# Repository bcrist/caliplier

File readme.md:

# Digital Caliper USB interface & LED Display

This project interfaces with the serial data output port found on cheap digital calipers.  It does several things:

* Provides power to the calipers
* Provides a second readout which isn't physically constrained by the measurement location/orientation
* Emulates a USB HID keyboard and "types" the current measurement at the press of a button
* Emulates a USB CDC-ACM serial port for logging/debug

There are many different variations on the serial format output by different calipers.  Some use 24-bit integers, some use BCD.  Some always output in inches, some always in mm, and some in whatever format the internal display is currently using.  Some include error detection data, others don't.  Currently there is only one protocol supported:

* Data signal is stable whenever Clock signal is high
* 24-bit packet, transferred over 8.1ms (+/- 0.1ms)
* First bit is always 1
* Next 20 bits are the unsigned magnitude (little-endian)
* Next bit is 1 if negative
* Last two bits are unused
* There is no indication whether it is in mm or inches mode.  In mm mode, 1 ULP is 0.01mm, and in inches mode, 1 ULP is 0.0005".
* The bus is idle for at least 5ms between packets

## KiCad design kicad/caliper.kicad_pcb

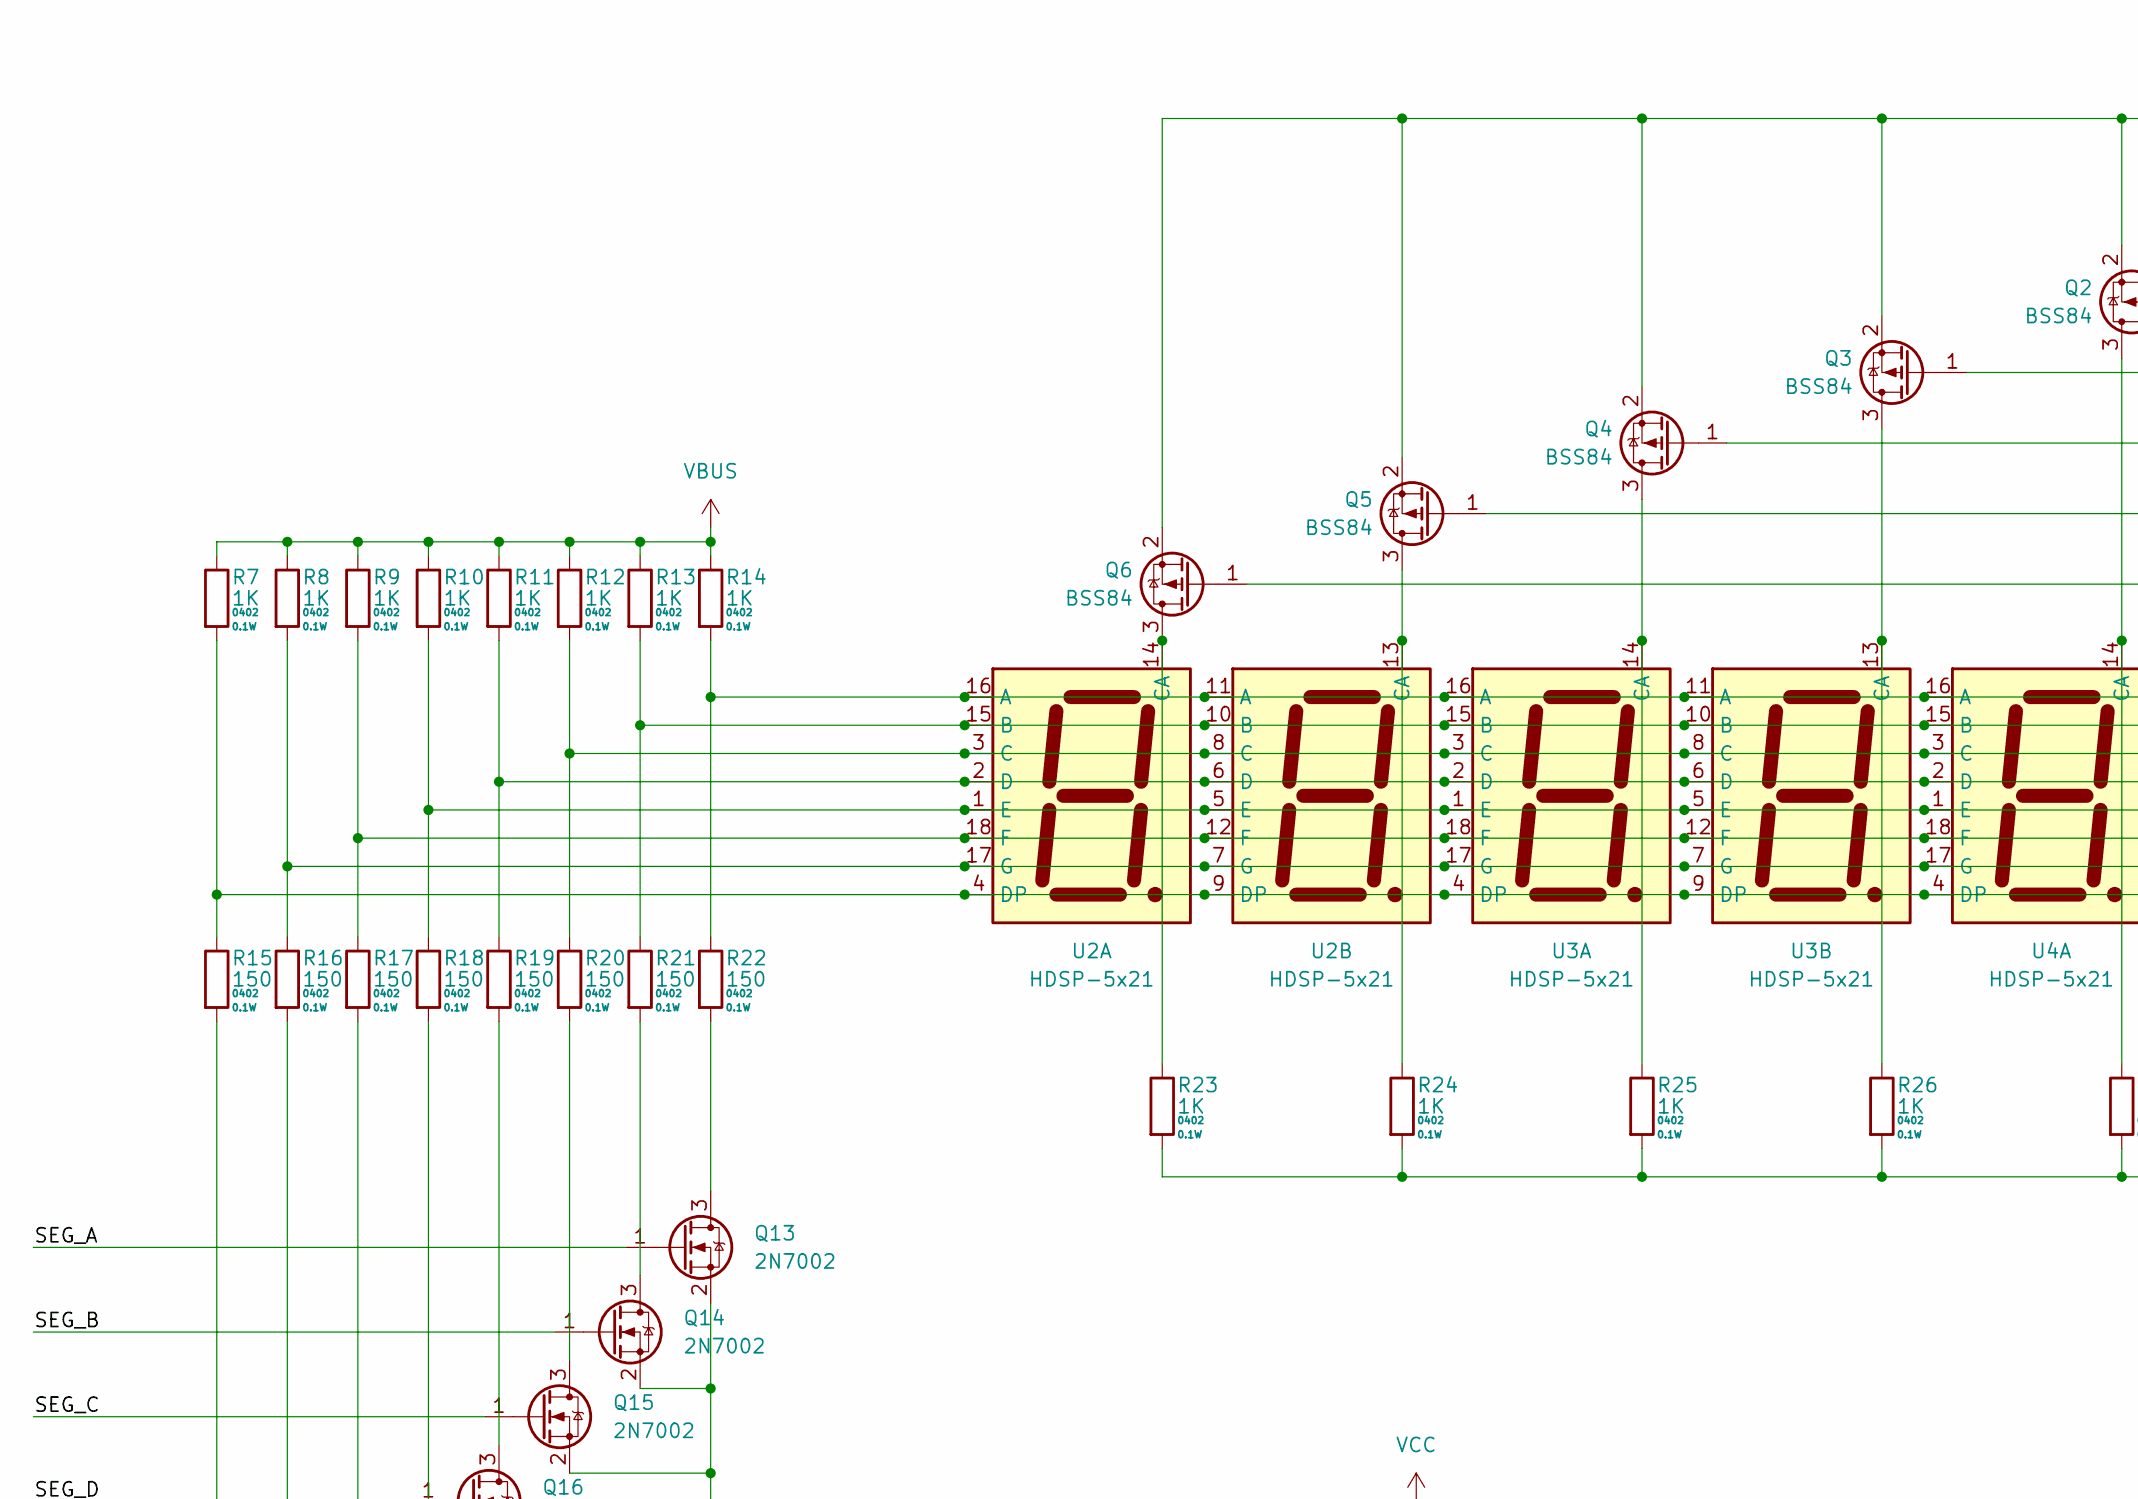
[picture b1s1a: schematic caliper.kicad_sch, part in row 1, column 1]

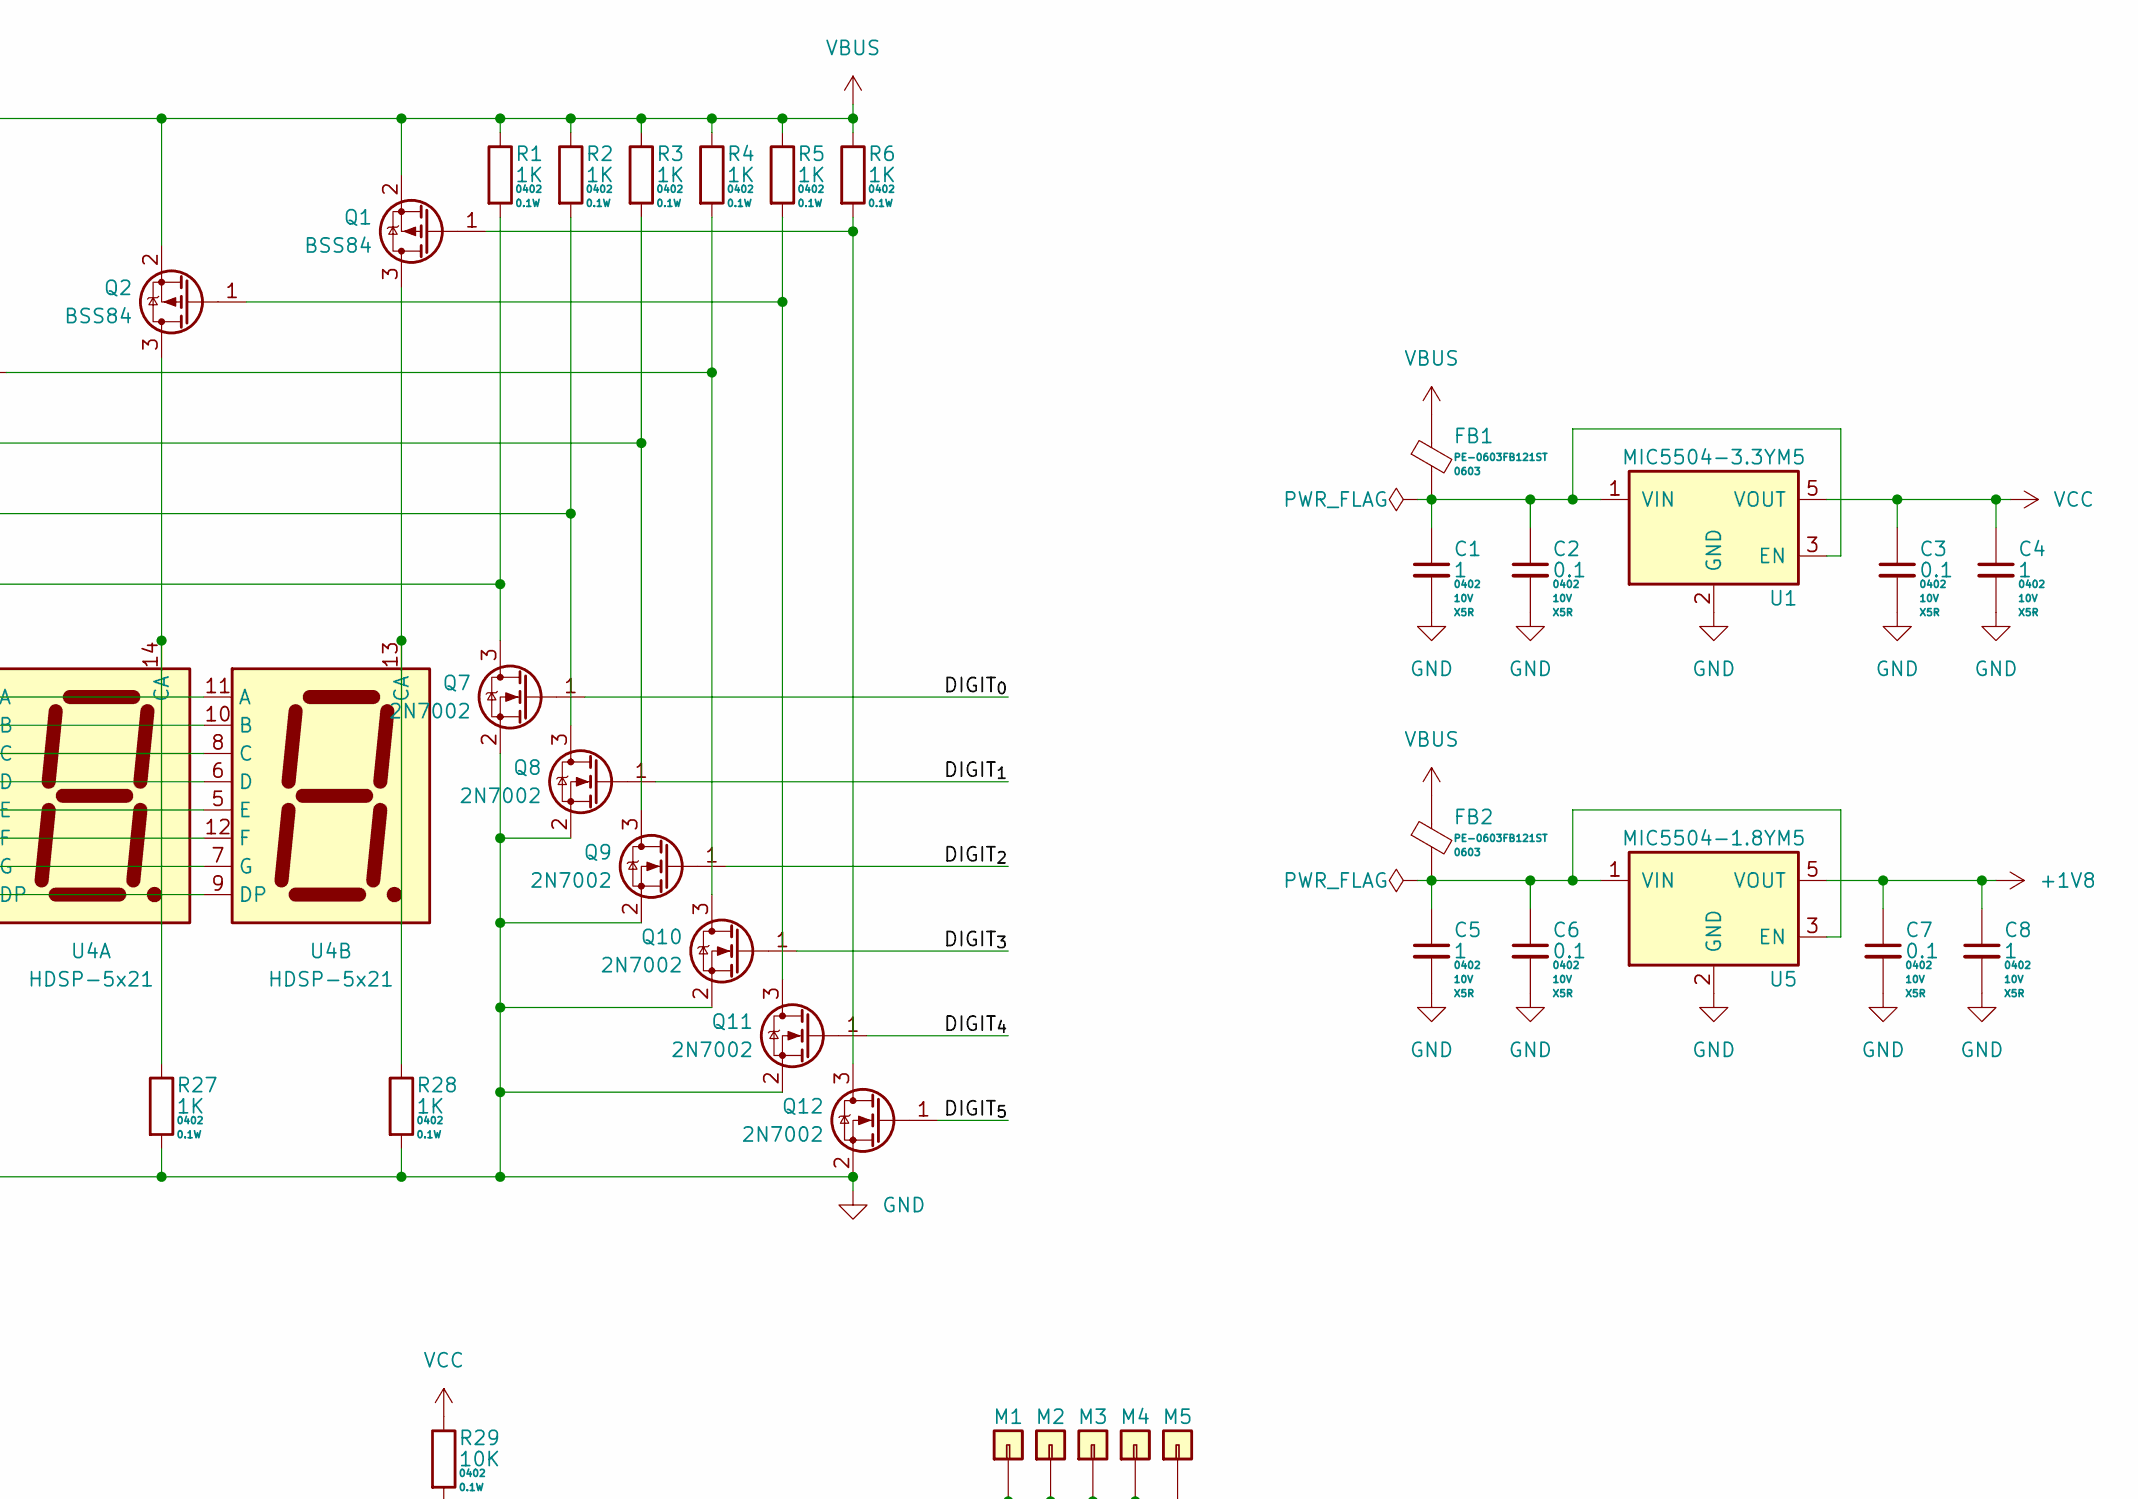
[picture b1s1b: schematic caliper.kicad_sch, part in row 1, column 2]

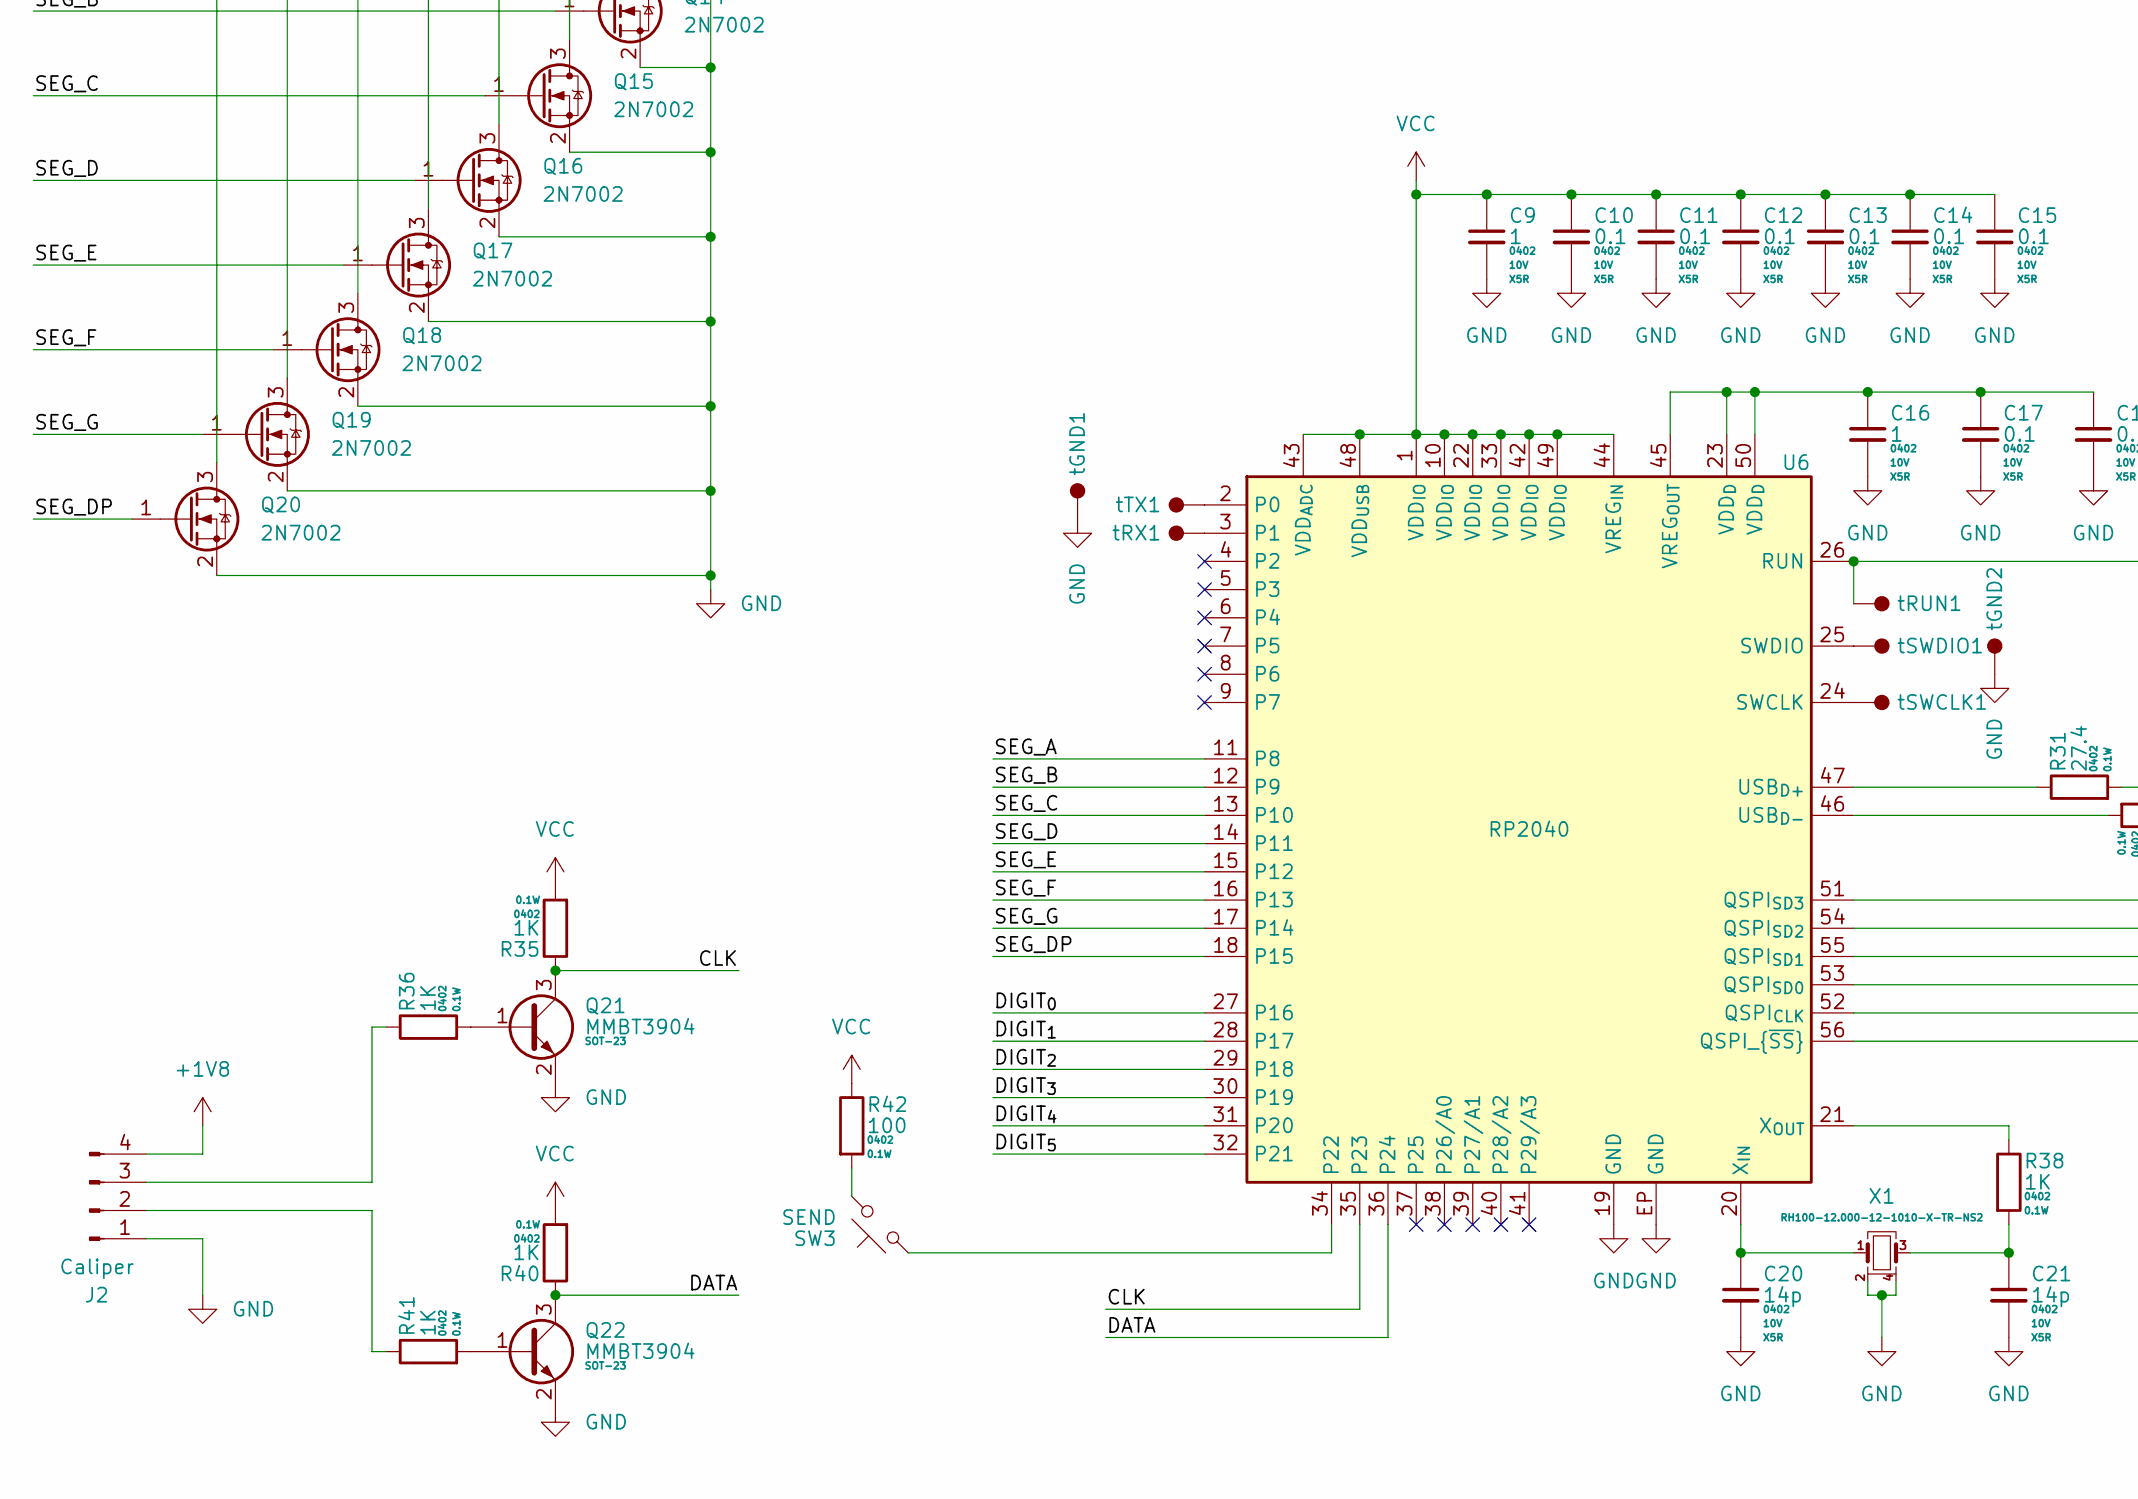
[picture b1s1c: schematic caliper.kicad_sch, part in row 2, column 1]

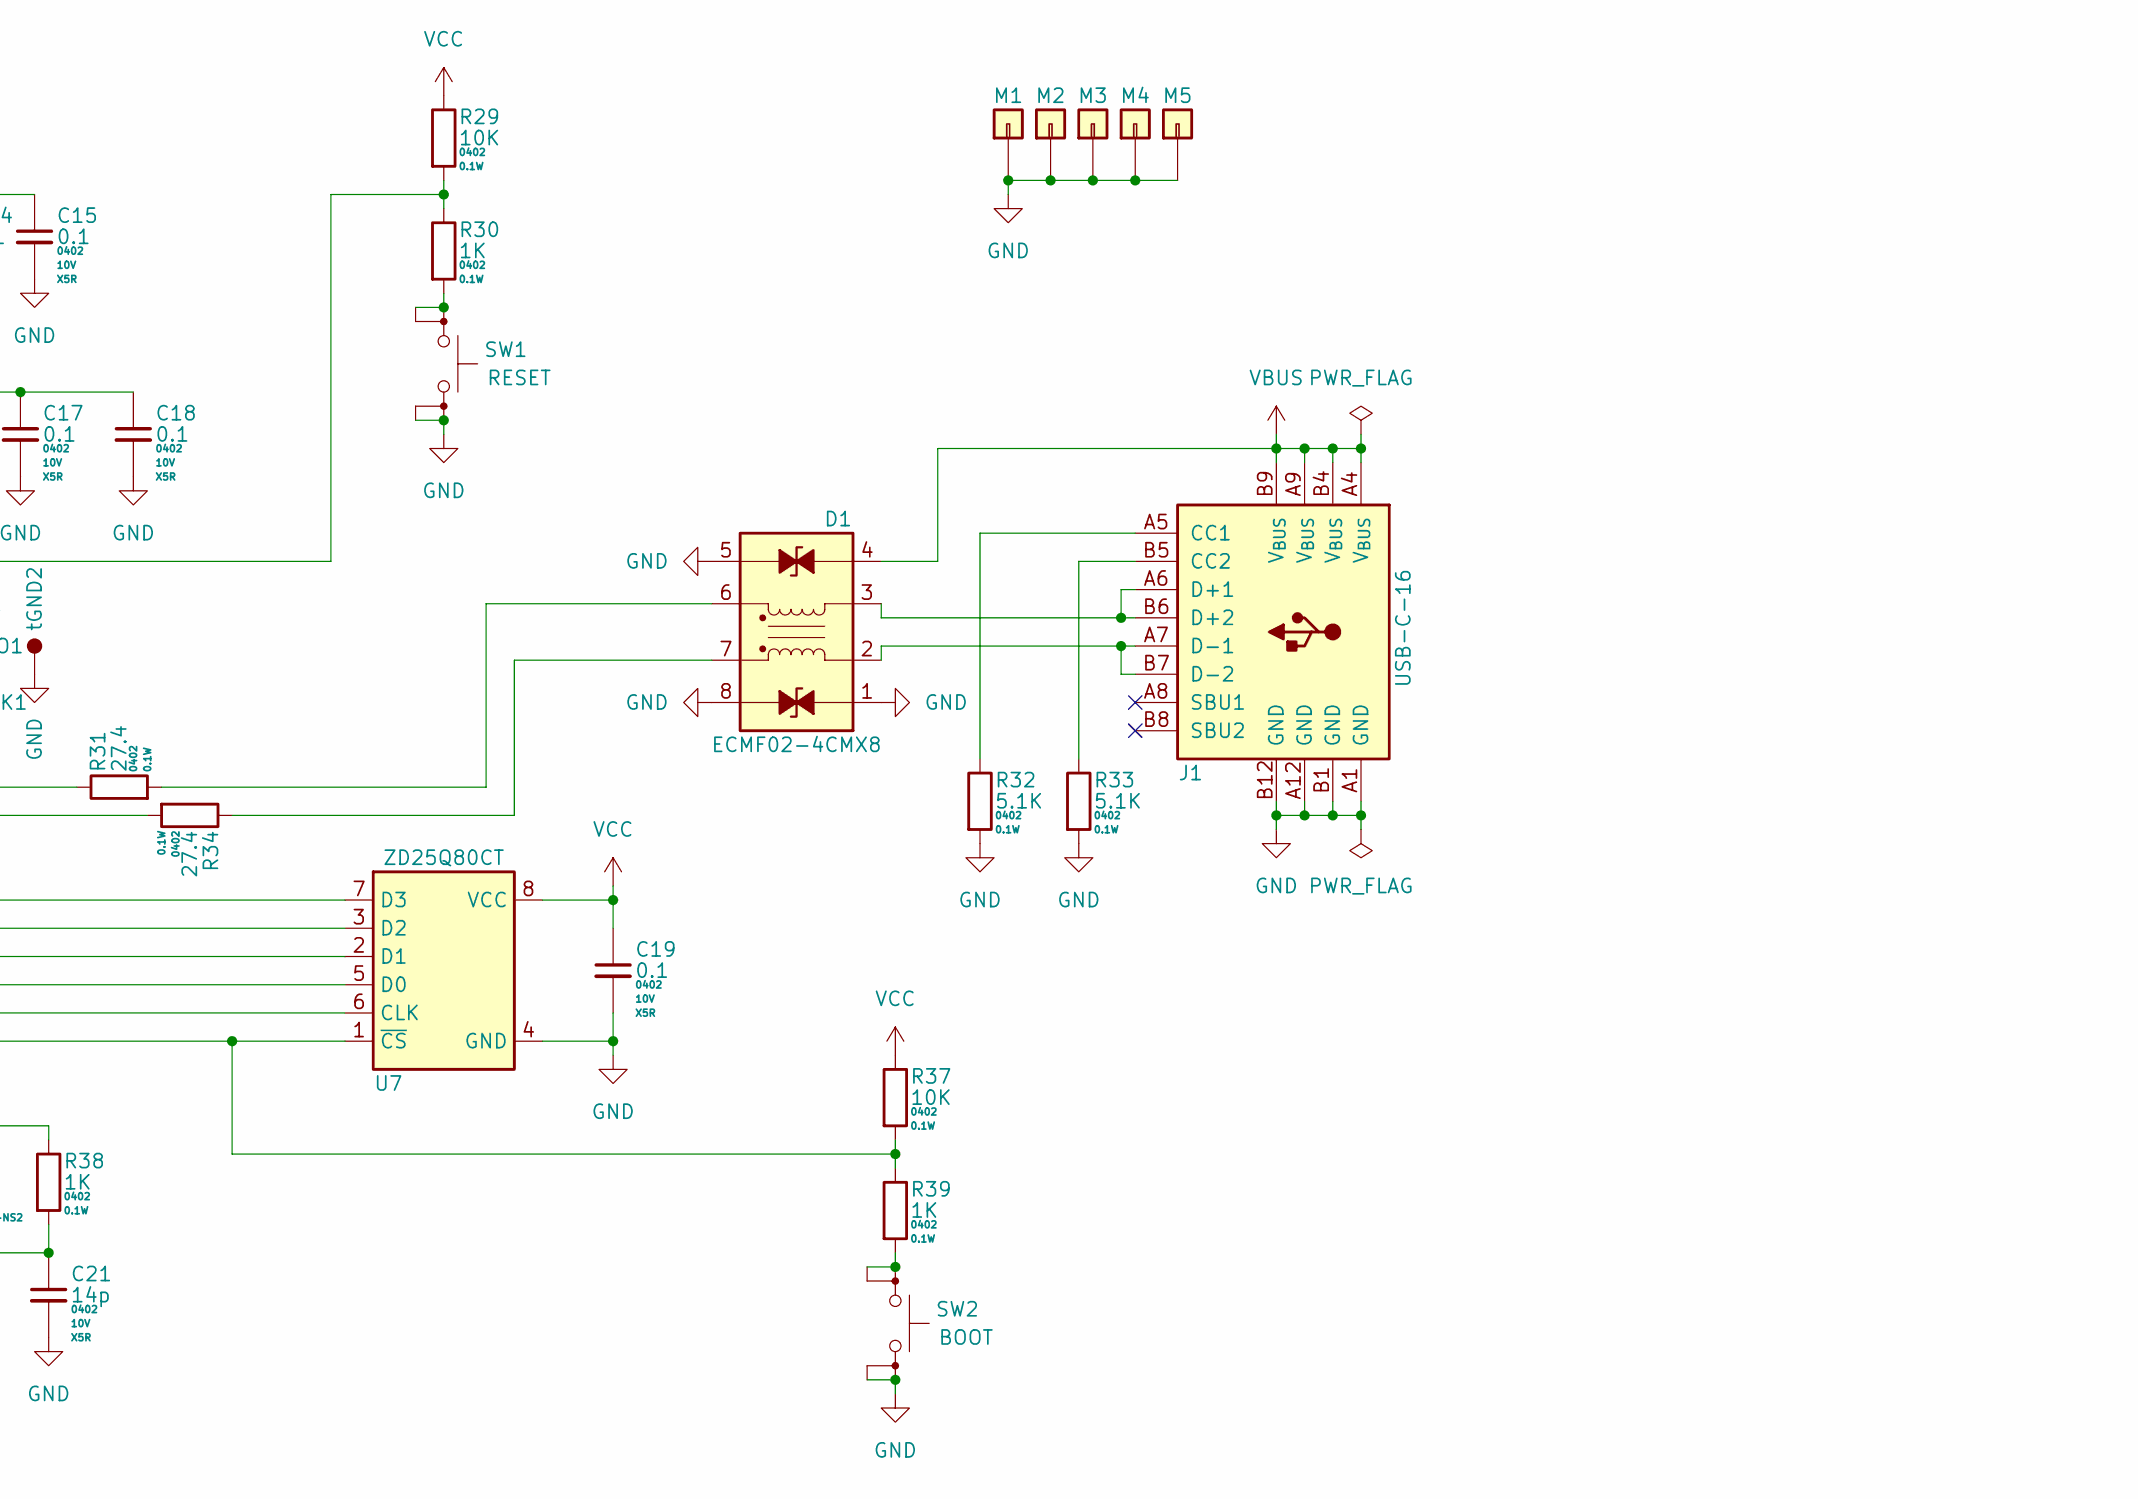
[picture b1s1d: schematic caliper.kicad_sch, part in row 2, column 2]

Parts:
C1, C4, C5, C8, C9, C16: 1; C_0402; Voltage 10V
C2, C3, C6, C7, C10, C11, C12, C13, C14, C15, C17, C18, C19: 0.1; C_0402; Voltage 10V
C20, C21: 14p; C_0402; Voltage 10V
D1: ECMF02-4CMX8; DFN-8-2.5x1.2-P0.45
FB1, FB2: PE-0603FB121ST; L_0603
J1: USB-C-16; USB_GCT_USB4085-FG-A
J2: Caliper; PinHeader_1x04_P2.54mm_Vertical
M1, M2, M3, M4, M5: GND; MountingHole_3.2mm_M3_Pad_Via
Q1, Q2, Q3, Q4, Q5, Q6: BSS84; SOT-23
Q7, Q8, Q9, Q10, Q11, Q12, Q13, Q14, Q15, Q16, Q17, Q18, Q19, Q20: 2N7002; SOT-23
Q21, Q22: MMBT3904; SOT-23
R1, R2, R3, R4, R5, R6, R7, R8, R9, R10, R11, R12, R13, R14, R23, R24, R25, R26, R27, R28, R30, R35, R36, R38, R39, R40, R41: 1K; R_0402
R15, R16, R17, R18, R19, R20, R21, R22: 150; R_0402
R29, R37: 10K; R_0402
R31, R34: 27.4; R_0402
R32, R33: 5.1K; R_0402
R42: 100; R_0402
SW1: RESET; SW_CK_PTS526_SM15
SW2: BOOT; SW_CK_PTS526_SM15
SW3: SEND; SW_Cherry_MX1A_1.00u_Plate_Centered
U1: MIC5504-3.3YM5; SOT-23-5
U2, U3, U4: HDSP-5x21
U5: MIC5504-1.8YM5; SOT-23-5
U6: RP2040; QFN-56-EP-7x7-P0.4
U7: ZD25Q80CT; SOP-8-4.9x3.9-P1.27
X1: RH100-12.000-12-1010-X-TR-NS2
tGND1, tGND2: GND; TestPoint
tRUN1: VCC; TestPoint
tRX1: RX; TestPoint
tSWCLK1: SWCLK; TestPoint
tSWDIO1: SWDIO; TestPoint
tTX1: TX; TestPoint

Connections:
+1V8: C7.1, C8.1, J2.4, U5.5 (VOUT)
/CLK: Q21.3 (C), R35.1, U6.35 (P23)
/DATA: Q22.3 (C), R40.1, U6.36 (P24)
/DIGIT_{0}: Q7.1 (G), U6.27 (P16)
/DIGIT_{1}: Q8.1 (G), U6.28 (P17)
/DIGIT_{2}: Q9.1 (G), U6.29 (P18)
/DIGIT_{3}: Q10.1 (G), U6.30 (P19)
/DIGIT_{4}: Q11.1 (G), U6.31 (P20)
/DIGIT_{5}: Q12.1 (G), U6.32 (P21)
/SEG_A: Q13.1 (G), U6.11 (P8)
/SEG_B: Q14.1 (G), U6.12 (P9)
/SEG_C: Q15.1 (G), U6.13 (P10)
/SEG_D: Q16.1 (G), U6.14 (P11)
/SEG_DP: Q20.1 (G), U6.18 (P15)
/SEG_E: Q17.1 (G), U6.15 (P12)
/SEG_F: Q18.1 (G), U6.16 (P13)
/SEG_G: Q19.1 (G), U6.17 (P14)
GND: C1.2, C2.2, C3.2, C4.2, C5.2, C6.2, C7.2, C8.2, C9.2, C10.2, C11.2, C12.2, C13.2, C14.2, C15.2, C16.2, C17.2, C18.2, C19.2, C20.2, C21.2, D1.1, D1.5, D1.8, J1.A1 (GND), J1.A12 (GND), J1.B1 (GND), J1.B12 (GND), J2.1, M1.1, M2.1, M3.1, M4.1, M5.1, Q7.2 (S), Q8.2 (S), Q9.2 (S), Q10.2 (S), Q11.2 (S), Q12.2 (S), Q13.2 (S), Q14.2 (S), Q15.2 (S), Q16.2 (S), Q17.2 (S), Q18.2 (S), Q19.2 (S), Q20.2 (S), Q21.2 (E), Q22.2 (E), R23.2, R24.2, R25.2, R26.2, R27.2, R28.2, R32.2, R33.2, SW1.3, SW1.4, SW2.3, SW2.4, U1.2 (GND), U5.2 (GND), U6.19 (GND), U6.EP (GND), U7.4 (GND), X1.2, X1.4, tGND1.1, tGND2.1
unnamed: C21.1, R38.2, X1.3
unnamed: D1.6, R31.2
unnamed: D1.7, R34.1
unnamed: J1.A5 (CC1), R32.1
unnamed: J1.B5 (CC2), R33.1
unnamed: D1.3, J1.A6 (D+1), J1.B6 (D+2)
unnamed: D1.2, J1.A7 (D-1), J1.B7 (D-2)
unnamed: J2.2, R41.1
unnamed: J2.3, R36.1
unnamed: Q1.3 (D), R28.1, U4.13 (CA)
unnamed: Q1.1 (G), Q12.3 (D), R6.2
unnamed: Q2.3 (D), R27.1, U4.14 (CA)
unnamed: Q3.3 (D), R26.1, U3.13 (CA)
unnamed: Q4.3 (D), R25.1, U3.14 (CA)
unnamed: Q4.1 (G), Q9.3 (D), R3.2
unnamed: Q5.3 (D), R24.1, U2.13 (CA)
unnamed: Q5.1 (G), Q8.3 (D), R2.2
unnamed: Q6.3 (D), R23.1, U2.14 (CA)
unnamed: Q6.1 (G), Q7.3 (D), R1.2
unnamed: Q3.1 (G), Q10.3 (D), R4.2
unnamed: Q2.1 (G), Q11.3 (D), R5.2
unnamed: Q13.3 (D), R22.2
unnamed: Q14.3 (D), R21.2
unnamed: Q15.3 (D), R20.2
unnamed: Q16.3 (D), R19.2
unnamed: Q17.3 (D), R18.2
unnamed: Q18.3 (D), R17.2
unnamed: Q19.3 (D), R16.2
unnamed: Q20.3 (D), R15.2
unnamed: Q21.1 (B), R36.2
unnamed: Q22.1 (B), R41.2
unnamed: R30.2, SW1.1, SW1.2
unnamed: R39.2, SW2.1, SW2.2
unnamed: R42.2, SW3.2
unnamed: C1.1, C2.1, FB1.2, U1.1 (VIN), U1.3 (EN)
unnamed: R14.2, R22.1, U2.11 (A), U2.16 (A), U3.11 (A), U3.16 (A), U4.11 (A), U4.16 (A)
unnamed: R13.2, R21.1, U2.10 (B), U2.15 (B), U3.10 (B), U3.15 (B), U4.10 (B), U4.15 (B)
unnamed: R12.2, R20.1, U2.3 (C), U2.8 (C), U3.3 (C), U3.8 (C), U4.3 (C), U4.8 (C)
unnamed: R11.2, R19.1, U2.2 (D), U2.6 (D), U3.2 (D), U3.6 (D), U4.2 (D), U4.6 (D)
unnamed: R7.2, R15.1, U2.4 (DP), U2.9 (DP), U3.4 (DP), U3.9 (DP), U4.4 (DP), U4.9 (DP)
unnamed: R10.2, R18.1, U2.1 (E), U2.5 (E), U3.1 (E), U3.5 (E), U4.1 (E), U4.5 (E)
unnamed: R9.2, R17.1, U2.12 (F), U2.18 (F), U3.12 (F), U3.18 (F), U4.12 (F), U4.18 (F)
unnamed: R8.2, R16.1, U2.7 (G), U2.17 (G), U3.7 (G), U3.17 (G), U4.7 (G), U4.17 (G)
unnamed: C5.1, C6.1, FB2.2, U5.1 (VIN), U5.3 (EN)
unnamed: U6.2 (P0), tTX1.1
unnamed: U6.3 (P1), tRX1.1
unnamed: SW3.1, U6.34 (P22)
unnamed: U6.52 (QSPI_{CLK}), U7.6 (CLK)
unnamed: U6.53 (QSPI_{SD0}), U7.5 (D0)
unnamed: U6.55 (QSPI_{SD1}), U7.2 (D1)
unnamed: U6.54 (QSPI_{SD2}), U7.3 (D2)
unnamed: U6.51 (QSPI_{SD3}), U7.7 (D3)
unnamed: R37.2, R39.1, U6.56 (QSPI_{~SS}), U7.1 (~CS)
unnamed: R29.2, R30.1, U6.26 (RUN), tRUN1.1
unnamed: U6.24 (SWCLK), tSWCLK1.1
unnamed: U6.25 (SWDIO), tSWDIO1.1
unnamed: R31.1, U6.47 (USB_{D+})
unnamed: R34.2, U6.46 (USB_{D-})
unnamed: C16.1, C17.1, C18.1, U6.23 (VDD_{D}), U6.45 (VREG_{OUT}), U6.50 (VDD_{D})
unnamed: C20.1, U6.20 (X_{IN}), X1.1
unnamed: R38.1, U6.21 (X_{OUT})
VBUS: D1.4, FB1.1, FB2.1, J1.A4 (V_{BUS}), J1.A9 (V_{BUS}), J1.B4 (V_{BUS}), J1.B9 (V_{BUS}), Q1.2 (S), Q2.2 (S), Q3.2 (S), Q4.2 (S), Q5.2 (S), Q6.2 (S), R1.1, R2.1, R3.1, R4.1, R5.1, R6.1, R7.1, R8.1, R9.1, R10.1, R11.1, R12.1, R13.1, R14.1
VCC: C3.1, C4.1, C9.1, C10.1, C11.1, C12.1, C13.1, C14.1, C15.1, C19.1, R29.1, R35.2, R37.1, R40.2, R42.1, U1.5 (VOUT), U6.1 (VDD_{IO}), U6.10 (VDD_{IO}), U6.22 (VDD_{IO}), U6.33 (VDD_{IO}), U6.42 (VDD_{IO}), U6.43 (VDD_{ADC}), U6.44 (VREG_{IN}), U6.48 (VDD_{USB}), U6.49 (VDD_{IO}), U7.8 (VCC)

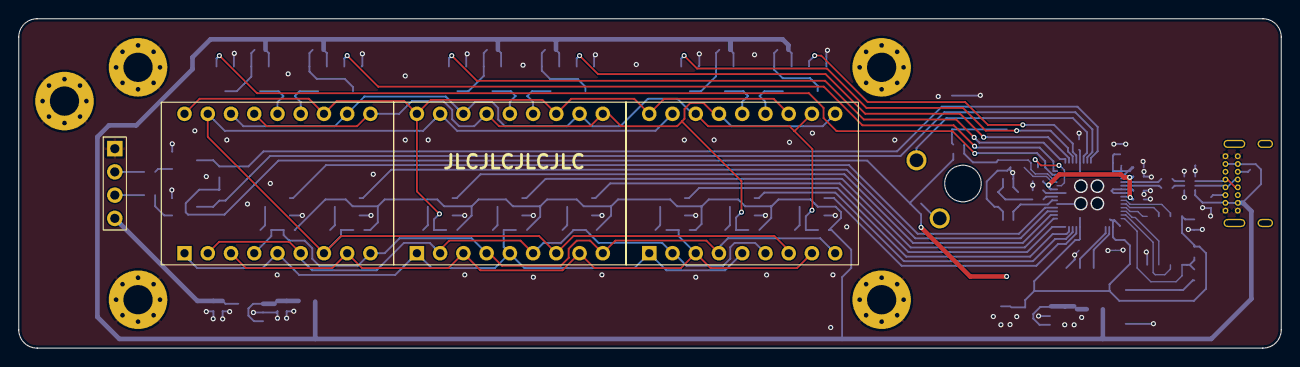
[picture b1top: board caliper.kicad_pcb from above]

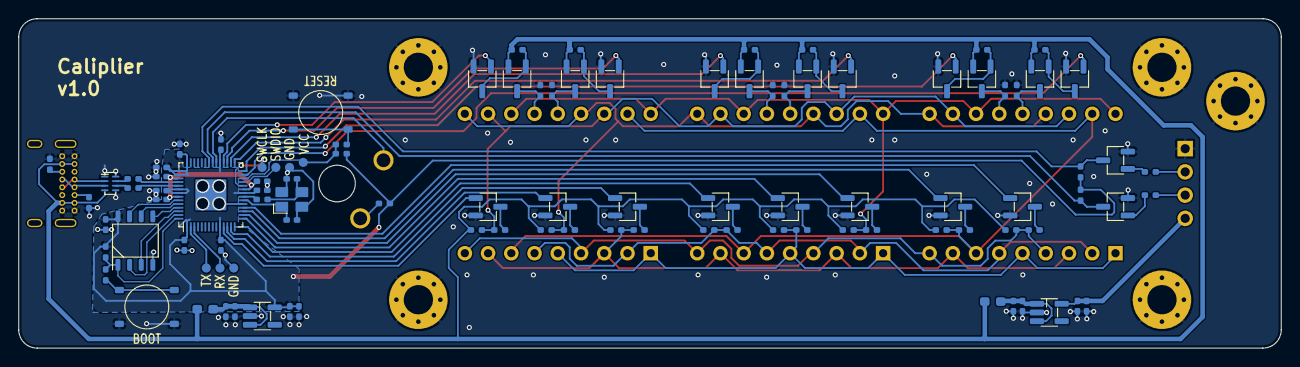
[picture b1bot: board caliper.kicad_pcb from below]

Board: 2 copper layers, 138.0 x 36.0 mm, 113 parts (102 on the bottom side), 81 nets.

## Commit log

2024-10-17 batman
2024-10-17 add image to readme
2024-10-17 Update readme.md
    clarify that magnitude bits are transferred LSB-first
